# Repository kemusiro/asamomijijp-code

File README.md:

# asamomijijp-code

[asamomiji.jp](https://asamomiji.jp/)の記事に付随する公開用ソースコードを管理するリポジトリです。記事中の短いコード例ではなく、複数ファイルからなる完全版、検証用コード、過去にGitで管理されていなかった自作プログラムを主な対象とします。

コードは記事単位で`projects/<article-slug>/`へ配置します。歴史的コードについては、原作成時期、収録時の変換、検証環境、既知の制約を各プロジェクトのREADMEに記録します。

詳細は[リポジトリ運用方針](docs/repository-policy.md)を参照してください。

## 収録プロジェクト

- [YM2203サウンドモジュール](projects/ym2203-sound-module/README.md) — 採用Rev C/P2基板設計、C SDK・I2C HOSTプレーヤー、USB-MIDIと独立した再現・検証手順
- [超エレキ万博2026 展示版](projects/cho-eleki-expo-2026-clusters/README.md) — Pi 4車体進化、Pico 16台の車体・球体巡回描画、Pi 5の2画面、導入・監視・停止復旧コードとテスト
- [Terraformで構築するALBとprivate subnetのEC2](projects/terraform-aws-iac-basics/README.md) — VPC、public/private subnet、NAT Gateway、ALB、EC2を含むAWS学習用構成
- [AQM1602XA Arduino／MicroPythonクラス](projects/aqm1602-arduino-notes/README.md) — 文字表示・外字・スクロール・電源回路設定、Pico 2 W・UNO R4 WiFi／Minimaでの実機確認と自動テスト
- [UiFlow2生成Python→編集可能Block変換](projects/uiflow2-python-to-blocks/README.md) — Core2／UiFlow2 V2.5.3固定プロファイルの厳密変換、最善努力変換、`.m5f2`構造調査、Web IDE・実機検証記録
- [Raspberry Pi Pico 2 Wクラスタ実験](projects/raspberry-pi-pico-cluster/README.md) — Raspberry Pi 5と複数Pico 2 WによるMandelbrot／レイトレーシング並列計算、実測結果、進捗動画
- [Raspberry Pi Pico 2 WのMicroPython DMA実験](projects/raspberry-pi-pico-2-w-micropython-dma/README.md) — メモリー間DMA、PIO TX連携、PIO＋DMA簡易ロジックアナライザーのコードと実測ログ
- [MicroPythonコードエミッタの実機ベンチマーク](projects/micropython-performance-techniques/README.md) — Pico 2 W上でbytecode、native、Viper、Thumbインラインアセンブラを比較した検証コードと測定記録
- [MMLプレイヤー](projects/mml-player/README.md) — 2002年に作成したJava製MMLプレイヤーの歴史的ソースコード
- [micro:bit 5-queen](projects/microbit-five-queens/README.md) — 2018年にPythonとC++で5-queen問題を解いた実験コード

## ライセンス

所有者が作成して本リポジトリで公開するコードは、個別の明示がない限り[BSD 2-Clause License](LICENSE)に従います。第三者コードや別ライセンスの対象は、各プロジェクトで個別に明示します。

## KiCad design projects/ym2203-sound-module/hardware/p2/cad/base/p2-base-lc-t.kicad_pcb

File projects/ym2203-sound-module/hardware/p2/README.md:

# P2 採用設計 — base T / YM2203 module T / editor N、FAB U

編集可能なCADは`cad/`、発注に使ったCAMは`artifacts/*/gerbers/`。
ベース100×100mm・4層、音源100×80mm・2層、編集100×76mm・2層。基板各5枚、実装1セットを想定。
KiCad10.0.5。**発注済み・P2 HAL未移植・実機未受入**。Rev CのUF2をP2へ書かない。

[組立](ASSEMBLY.md)／[音声・機構](ASSEMBLY-AUDIO.md)／[互換性要件](COMPATIBILITY.md)／[発注条件](ORDER.md)／[一般BOM](procurement/README.md)。
[実装BOM](assembly/design-bom-1set.csv)は302参照、[G40](assembly/g40-pinout.csv)、[追加配線](assembly/module-wire-map.csv)、[GPIO](interfaces/gpio-map.csv)を併用する。

採用CAD/CAM、配線済み形状、原本の受入記録は変更していない。
`requirements/approved-topology.json`は採用した現在の全端子・値・フットプリントを固定する。旧レビューや購入カートを読む検査は不要。
`provenance/`は元の製造記録であり、移設後の検査入力ではない。元レポートの日時・ハッシュを更新して合格を装わない。

[ベース1枚図](readable/base/schematic.svg)／[音源1枚図](readable/module/schematic.svg)／[編集1枚図](readable/panel/schematic.svg)。

## 再現・検証

Python3とGerbonara1.6.3を使う。`<pcb-python>`は`pcbnew`をimportできるKiCad付属Python。
`<cam-python>`はGerbonaraを入れたPython。どちらも作業ディレクトリは本書の場所。

```sh
python3 tools/contract.py
python3 tools/test_contract.py
<pcb-python> tools/check_native.py
<cam-python> tools/verify_cam.py . --no-previews
<cam-python> tools/test_cam.py .
python3 tools/package.py
```

ZIPは`local-output/gerbers/`に再生成する。3件とも発注時ZIPとSHA-256が一致することを`expected-archives.json`で検査する。
新しいKiCad出力の検査は`tools/regenerate.py`を使う。正本を直接変更せず別の作業コピーへ再出力し、ERC/DRC・回路図整合、全銅形状・穴・層構成を検査する。
Gerber再出力では作成時刻コメントだけ変わり得るため、発注ZIPの完全一致とCAD再出力の一致を区別する。

```sh
python3 tools/regenerate.py --work /tmp/p2-native-check --pcb-python <pcb-python> --cam-python <cam-python>
python3 readable/tools/generate.py base module panel
python3 readable/tools/check.py --boards base module panel
```

読図用の再生成コマンドは別の作業コピーで実行する。生成後のレポートは日時等が変わるため、配布時のソースハッシュ検査とは区別する。
旧配線試行や旧購入資料を用意する必要はない。読図用回路図は基板ごと1枚に再生成し、実際のネイティブ接続と照合する。
静的検査とモデル試験は電源・USB・音声・機構の実機試験を代替しない。

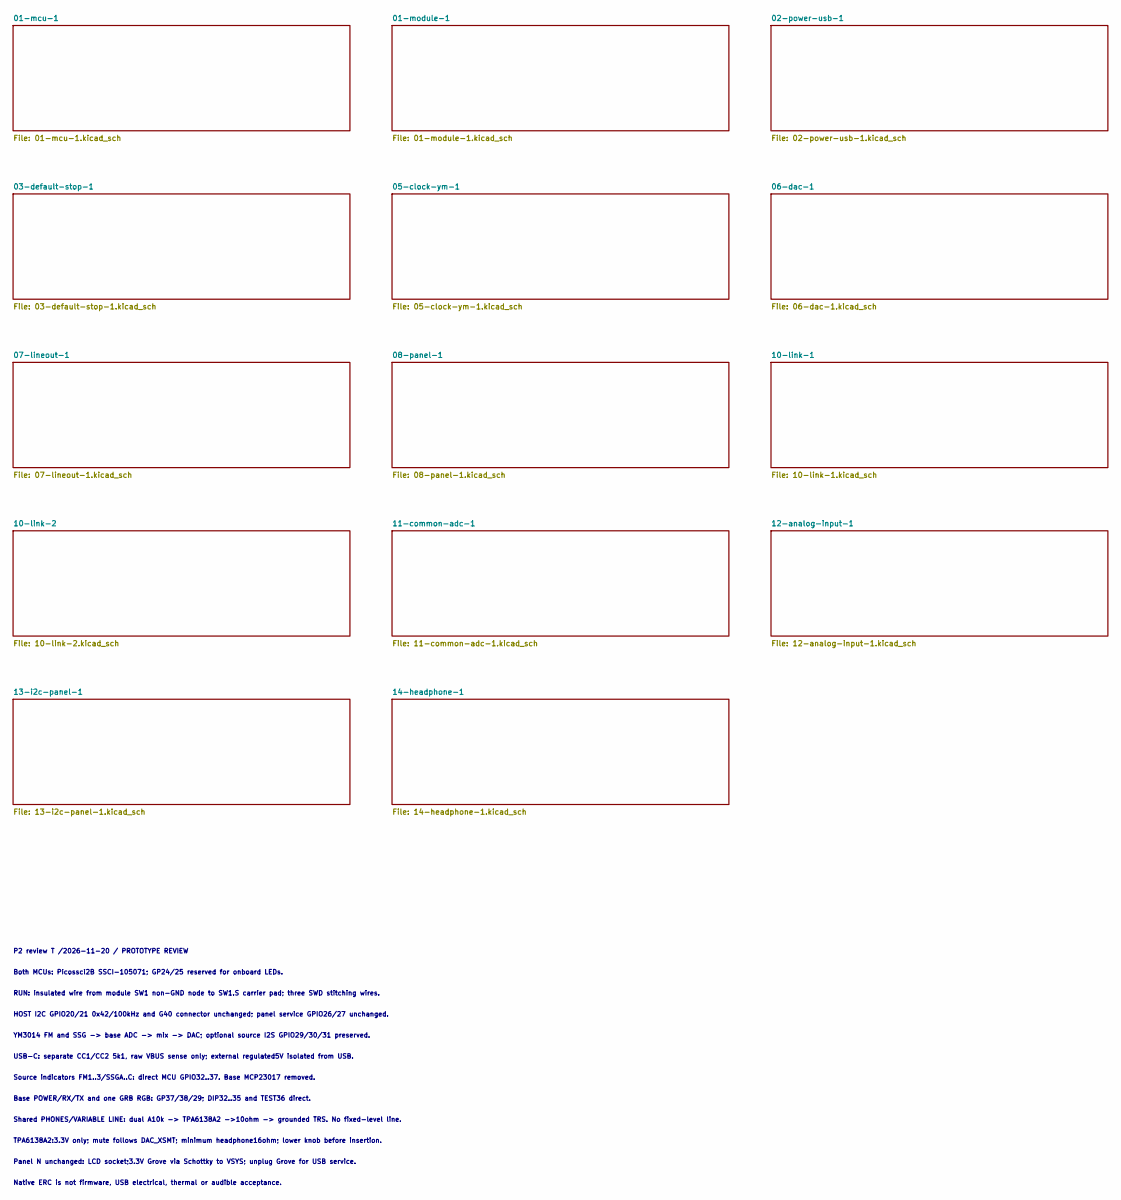
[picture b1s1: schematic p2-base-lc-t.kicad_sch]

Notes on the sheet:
P2 review T /2026-11-20 / PROTOTYPE REVIEW
Both MCUs: Picossci2B SSCI-105071; GP24/25 reserved for onboard LEDs.
RUN: insulated wire from module SW1 non-GND node to SW1.S carrier pad; three SWD stitching wires.
HOST I2C GPIO20/21 0x42/100kHz and G40 connector unchanged; panel service GPIO26/27 unchanged.
YM3014 FM and SSG -> base ADC -> mix -> DAC; optional source I2S GPIO29/30/31 preserved.
USB-C: separate CC1/CC2 5k1, raw VBUS sense only; external regulated5V isolated from USB.
Source indicators FM1..3/SSGA..C: direct MCU GPIO32..37. Base MCP23017 removed.
Base POWER/RX/TX and one GRB RGB: GP37/38/29; DIP32..35 and TEST36 direct.
Shared PHONES/VARIABLE LINE: dual A10k -> TPA6138A2 ->10ohm -> grounded TRS. No fixed-level line.
TPA6138A2:3.3V only; mute follows DAC_XSMT; minimum headphone16ohm; lower knob before insertion.
Panel N unchanged: LCD socket;3.3V Grove via Schottky to VSYS; unplug Grove for USB service.
Native ERC is not firmware, USB electrical, thermal or audible acceptance.

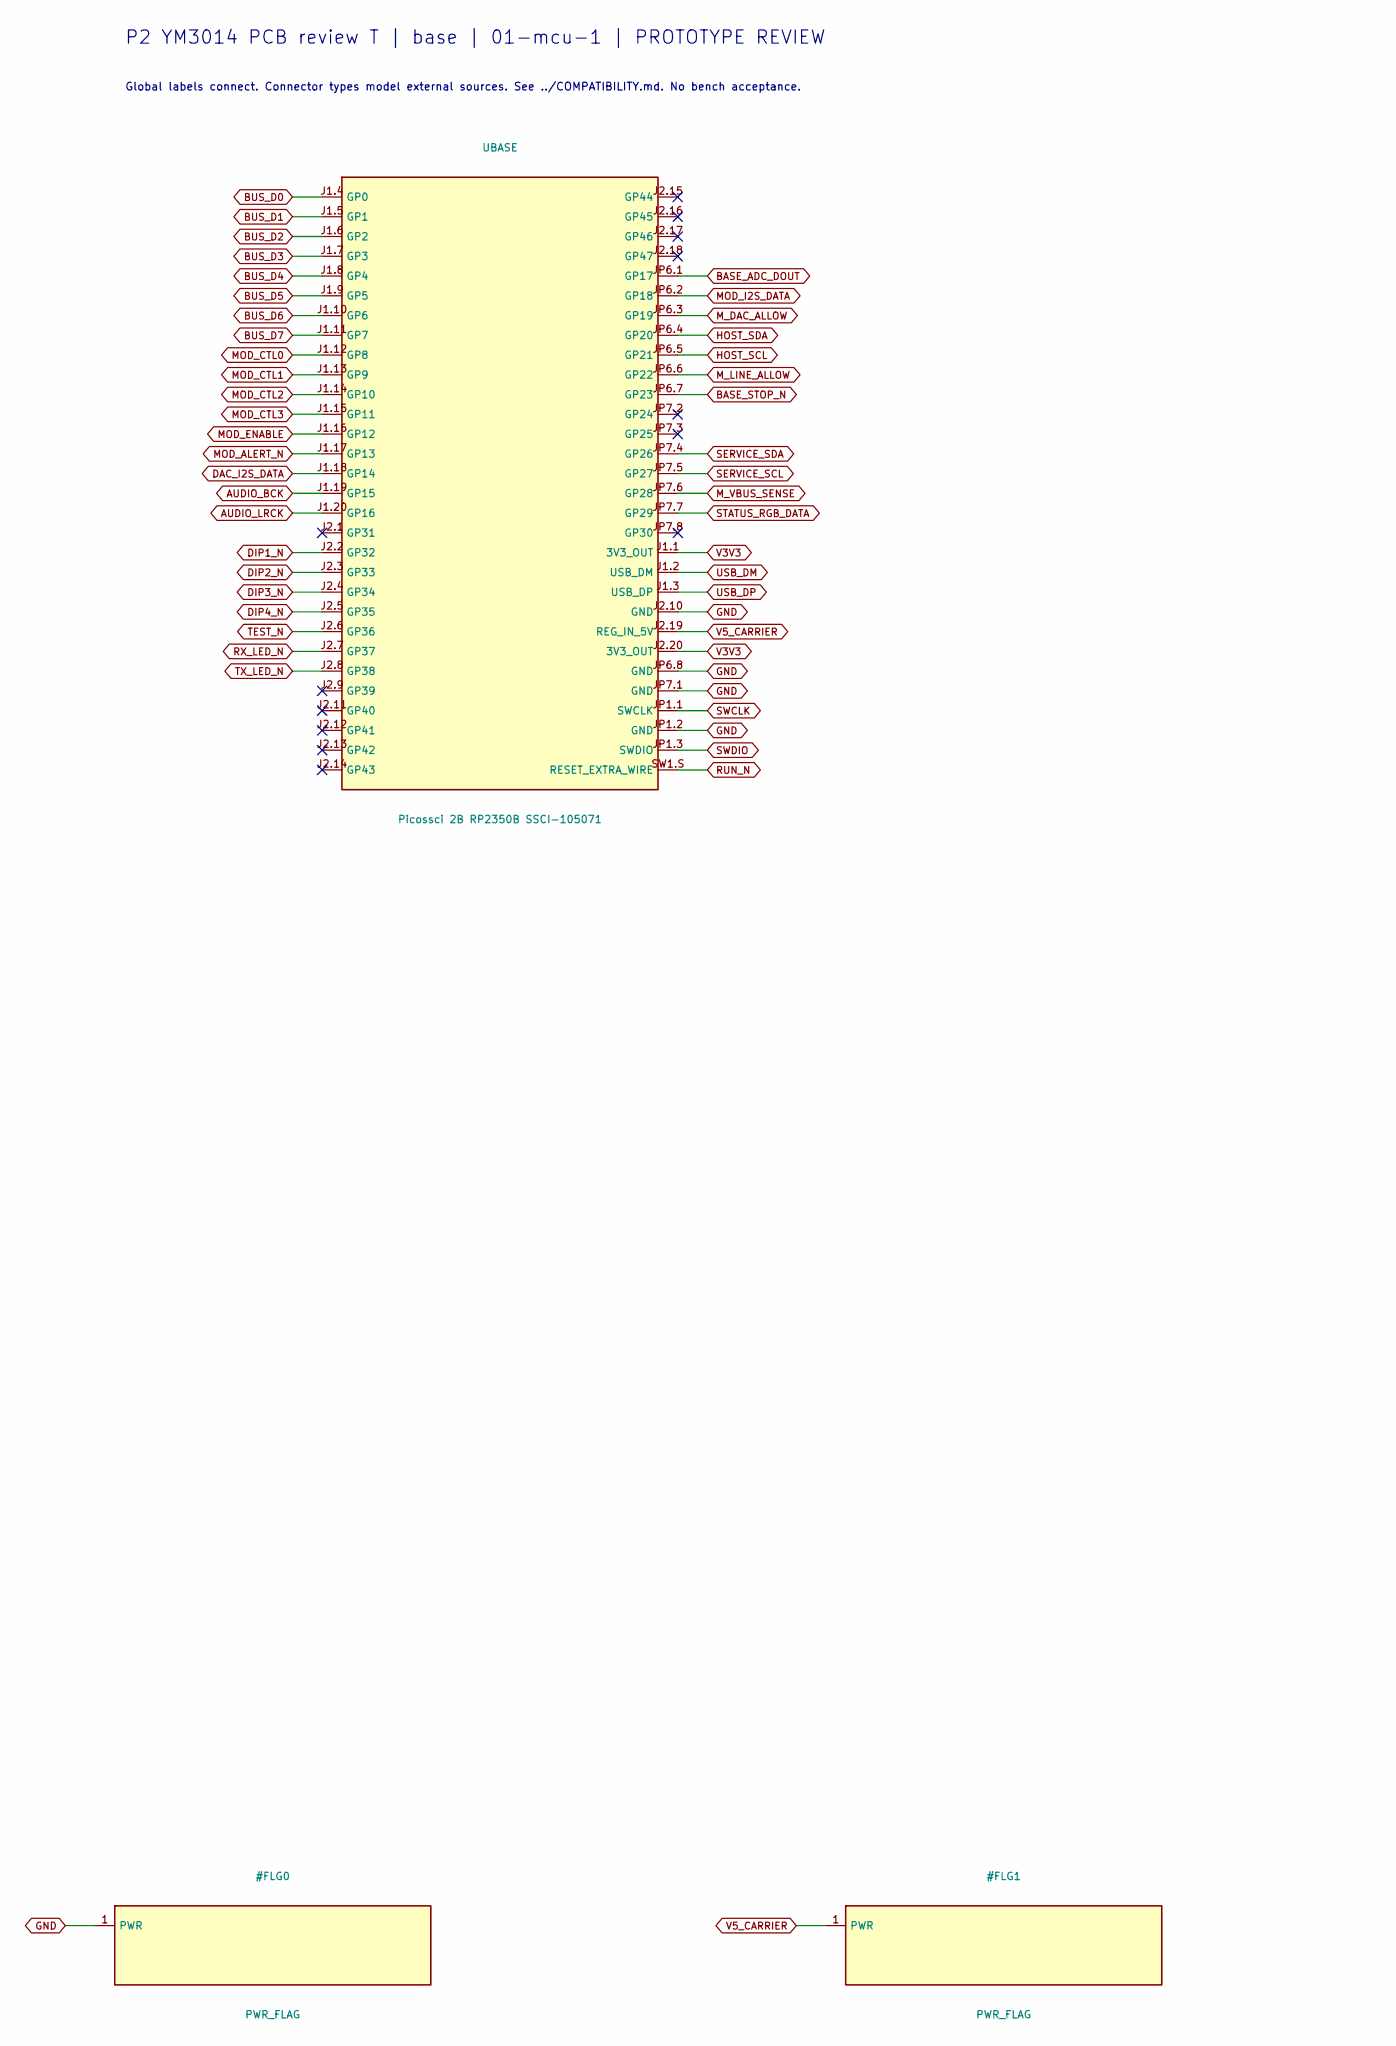
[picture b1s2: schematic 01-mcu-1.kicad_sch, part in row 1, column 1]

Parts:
UBASE: Picossci 2B RP2350B SSCI-105071; Picossci2B_DirectSolder_DebugWire

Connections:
AUDIO_BCK: UBASE.J1.19 (GP15); also elsewhere on the board
AUDIO_LRCK: UBASE.J1.20 (GP16); also elsewhere on the board
BASE_ADC_DOUT: UBASE.JP6.1 (GP17); also elsewhere on the board
BASE_STOP_N: UBASE.JP6.7 (GP23); also elsewhere on the board
BUS_D0: UBASE.J1.4 (GP0); also elsewhere on the board
BUS_D1: UBASE.J1.5 (GP1); also elsewhere on the board
BUS_D2: UBASE.J1.6 (GP2); also elsewhere on the board
BUS_D3: UBASE.J1.7 (GP3); also elsewhere on the board
BUS_D4: UBASE.J1.8 (GP4); also elsewhere on the board
BUS_D5: UBASE.J1.9 (GP5); also elsewhere on the board
BUS_D6: UBASE.J1.10 (GP6); also elsewhere on the board
BUS_D7: UBASE.J1.11 (GP7); also elsewhere on the board
DAC_I2S_DATA: UBASE.J1.18 (GP14); also elsewhere on the board
DIP1_N: UBASE.J2.2 (GP32); also elsewhere on the board
DIP2_N: UBASE.J2.3 (GP33); also elsewhere on the board
DIP3_N: UBASE.J2.4 (GP34); also elsewhere on the board
DIP4_N: UBASE.J2.5 (GP35); also elsewhere on the board
GND: UBASE.J2.10 (GND), UBASE.JP1.2 (GND), UBASE.JP6.8 (GND), UBASE.JP7.1 (GND); also elsewhere on the board
HOST_SCL: UBASE.JP6.5 (GP21); also elsewhere on the board
HOST_SDA: UBASE.JP6.4 (GP20); also elsewhere on the board
MOD_ALERT_N: UBASE.J1.17 (GP13); also elsewhere on the board
MOD_CTL0: UBASE.J1.12 (GP8); also elsewhere on the board
MOD_CTL1: UBASE.J1.13 (GP9); also elsewhere on the board
MOD_CTL2: UBASE.J1.14 (GP10); also elsewhere on the board
MOD_CTL3: UBASE.J1.15 (GP11); also elsewhere on the board
MOD_ENABLE: UBASE.J1.16 (GP12); also elsewhere on the board
MOD_I2S_DATA: UBASE.JP6.2 (GP18); also elsewhere on the board
M_DAC_ALLOW: UBASE.JP6.3 (GP19); also elsewhere on the board
M_LINE_ALLOW: UBASE.JP6.6 (GP22); also elsewhere on the board
M_VBUS_SENSE: UBASE.JP7.6 (GP28); also elsewhere on the board
RUN_N: UBASE.SW1.S (RESET_EXTRA_WIRE); also elsewhere on the board
RX_LED_N: UBASE.J2.7 (GP37); also elsewhere on the board
SERVICE_SCL: UBASE.JP7.5 (GP27); also elsewhere on the board
SERVICE_SDA: UBASE.JP7.4 (GP26); also elsewhere on the board
STATUS_RGB_DATA: UBASE.JP7.7 (GP29); also elsewhere on the board
SWCLK: UBASE.JP1.1 (SWCLK); also elsewhere on the board
SWDIO: UBASE.JP1.3 (SWDIO); also elsewhere on the board
TEST_N: UBASE.J2.6 (GP36); also elsewhere on the board
TX_LED_N: UBASE.J2.8 (GP38); also elsewhere on the board
USB_DM: UBASE.J1.2 (USB_DM); also elsewhere on the board
USB_DP: UBASE.J1.3 (USB_DP); also elsewhere on the board
V3V3: UBASE.J1.1 (3V3_OUT), UBASE.J2.20 (3V3_OUT); also elsewhere on the board
V5_CARRIER: UBASE.J2.19 (REG_IN_5V); also elsewhere on the board

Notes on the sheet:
P2 YM3014 PCB review T | base | 01-mcu-1 | PROTOTYPE REVIEW
Global labels connect. Connector types model external sources. See ../COMPATIBILITY.md. No bench acceptance.

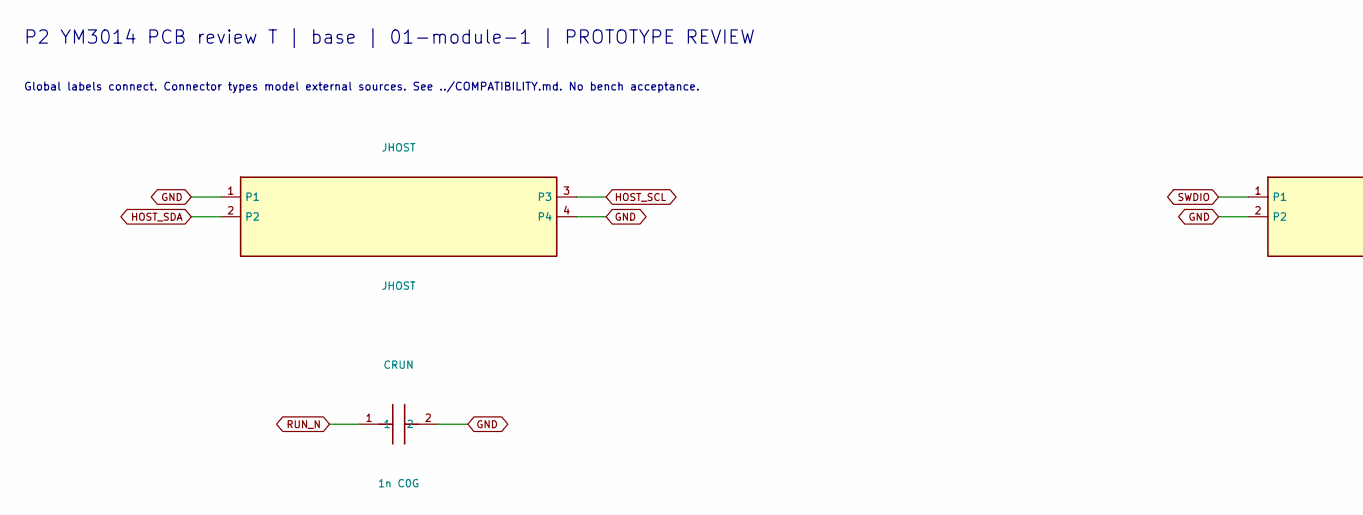
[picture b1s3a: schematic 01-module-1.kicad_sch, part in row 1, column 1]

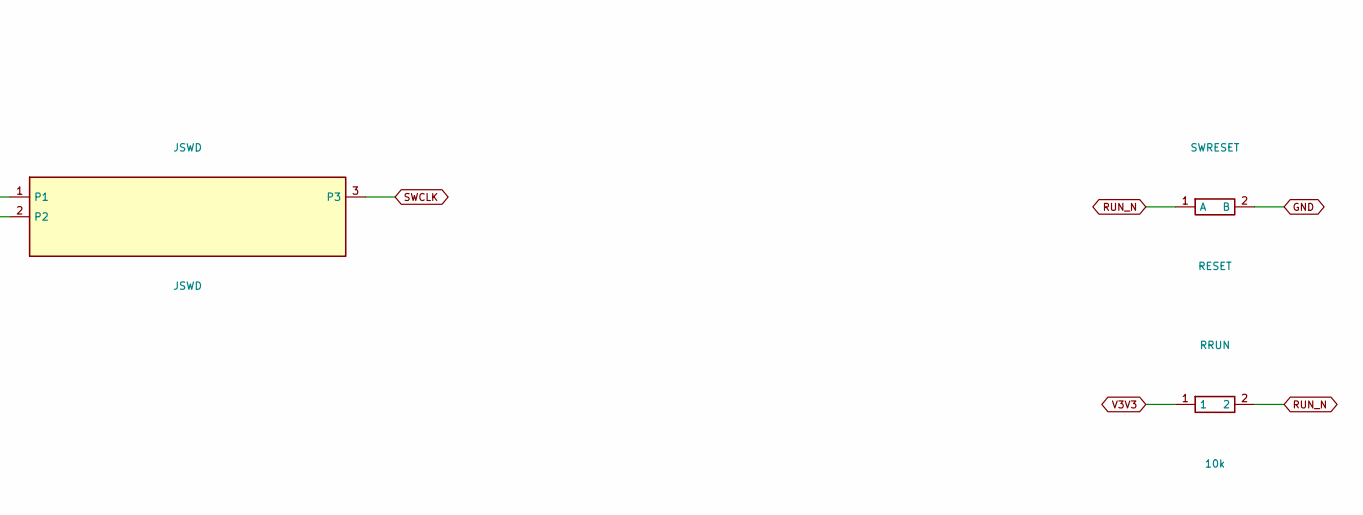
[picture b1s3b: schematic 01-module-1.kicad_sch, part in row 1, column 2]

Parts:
CRUN: 1n C0G; C_0805_2012Metric
JHOST: JHOST; PinHeader_1x04_P2.54mm_Vertical
JSWD: JSWD; PinHeader_1x03_P2.54mm_Vertical
RRUN: 10k; R_0805_2012Metric
SWRESET: RESET; SW_PUSH_6mm_H4.3mm

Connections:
GND: CRUN.2, JHOST.1, JHOST.4, JSWD.2, SWRESET.2 (B); also elsewhere on the board
HOST_SCL: JHOST.3; also elsewhere on the board
HOST_SDA: JHOST.2; also elsewhere on the board
RUN_N: CRUN.1, RRUN.2, SWRESET.1 (A); also elsewhere on the board
SWCLK: JSWD.3; also elsewhere on the board
SWDIO: JSWD.1; also elsewhere on the board
V3V3: RRUN.1; also elsewhere on the board

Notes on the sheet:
P2 YM3014 PCB review T | base | 01-module-1 | PROTOTYPE REVIEW
Global labels connect. Connector types model external sources. See ../COMPATIBILITY.md. No bench acceptance.

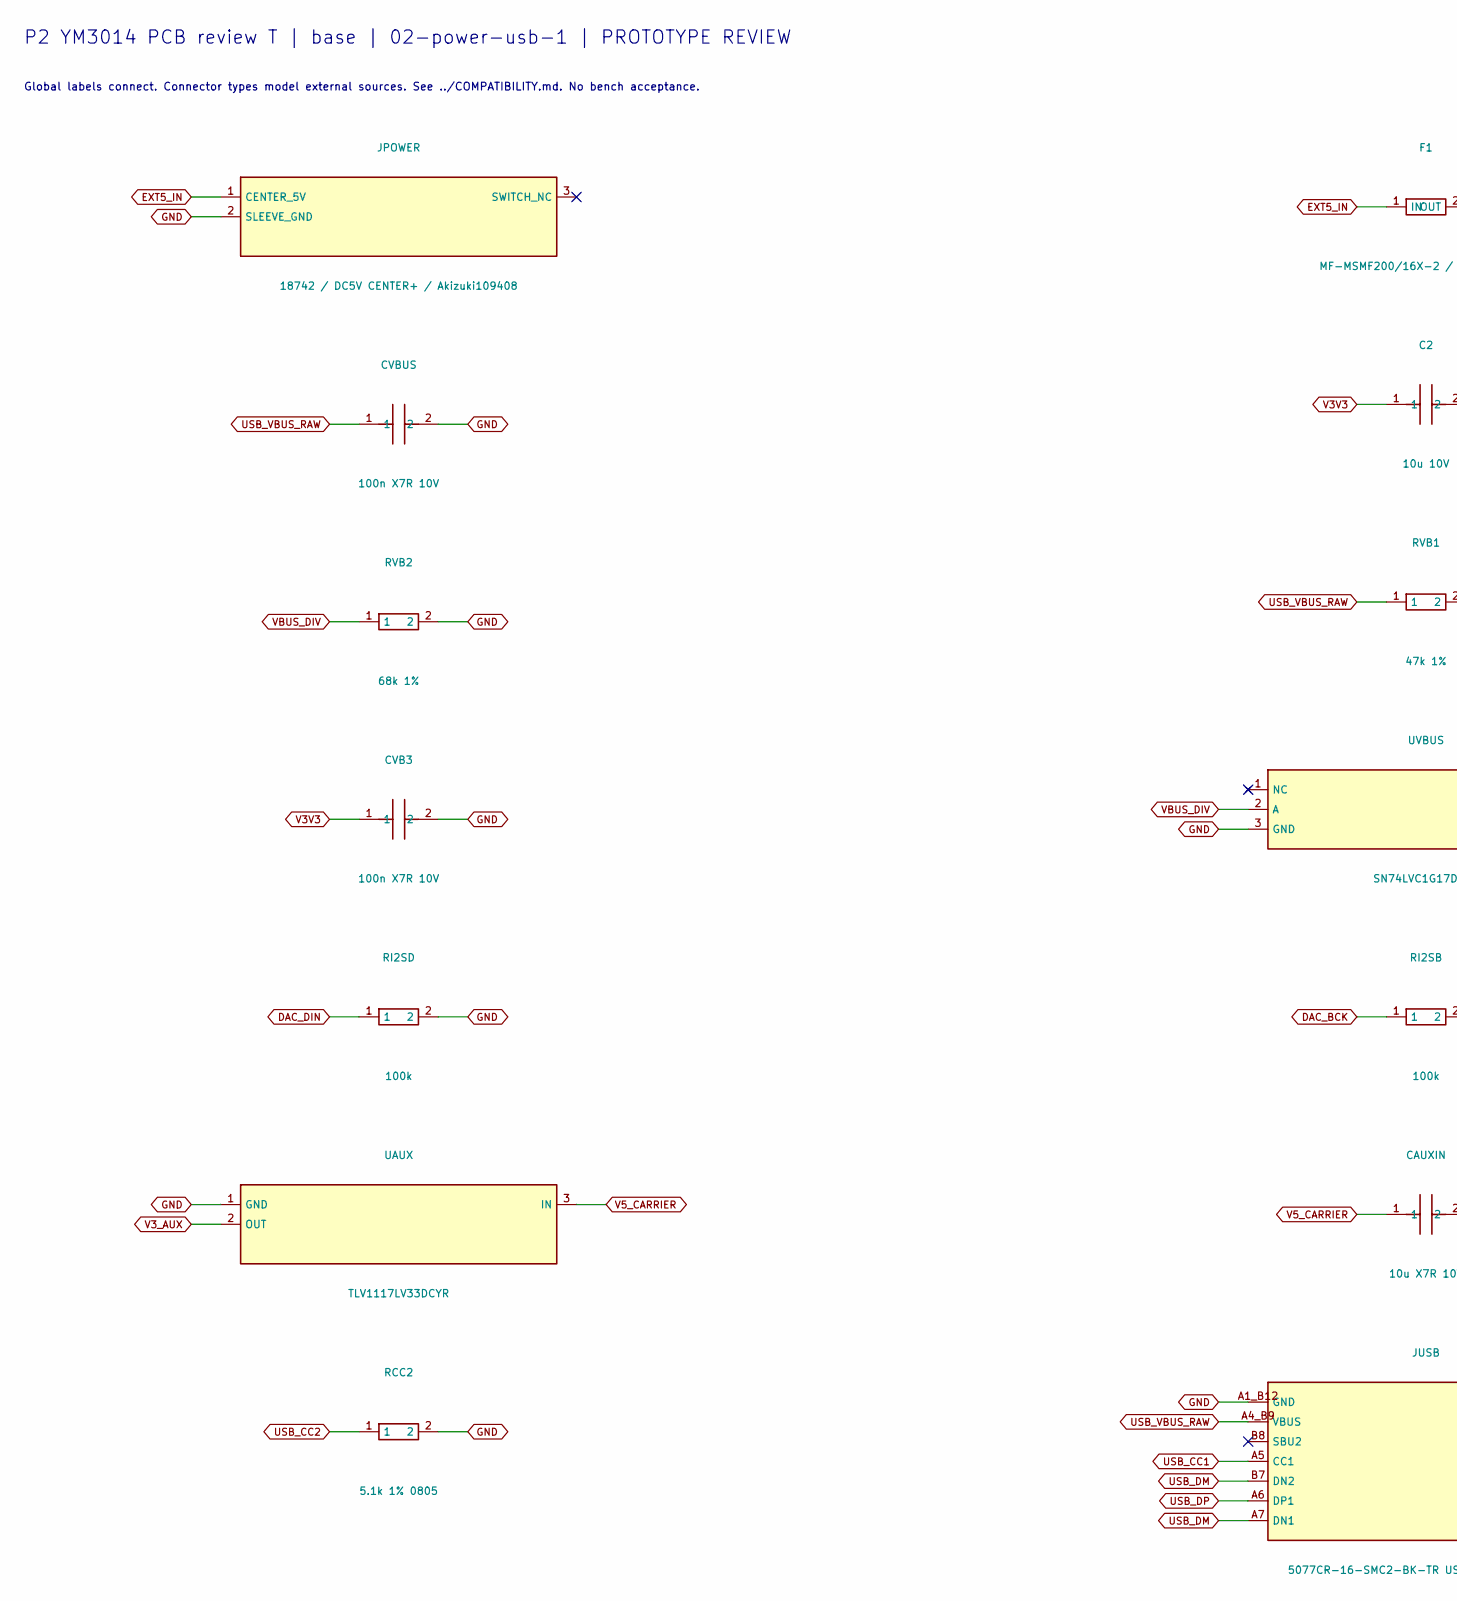
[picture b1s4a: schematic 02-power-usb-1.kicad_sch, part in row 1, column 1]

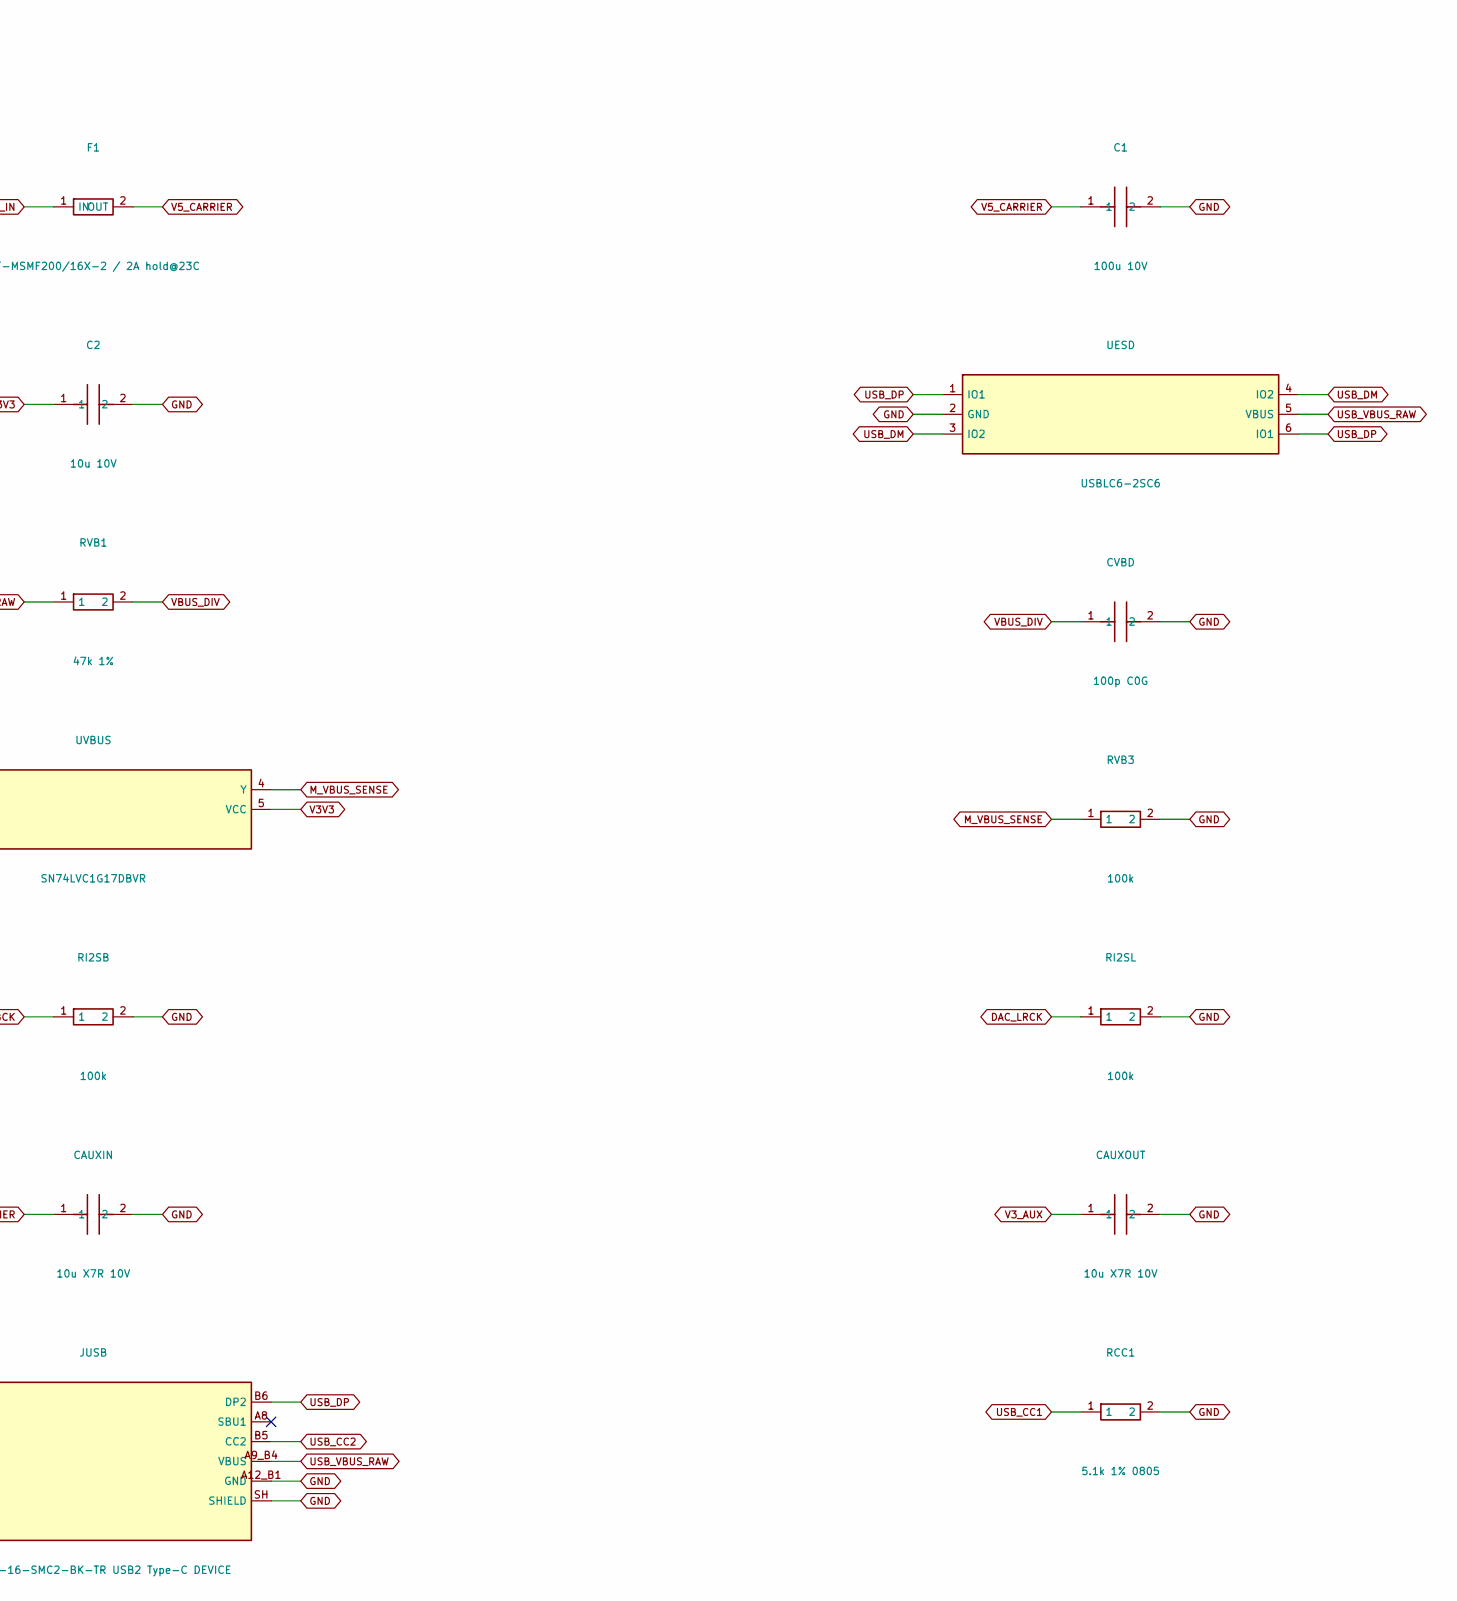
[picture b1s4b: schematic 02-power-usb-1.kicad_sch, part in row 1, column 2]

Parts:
C1: 100u 10V; CP_Radial_D6.3mm_P2.50mm
C2: 10u 10V; C_0805_2012Metric
CAUXIN: 10u X7R 10V; C_0805_2012Metric
CAUXOUT: 10u X7R 10V; C_0805_2012Metric
CVB3: 100n X7R 10V; C_0805_2012Metric
CVBD: 100p C0G; C_0805_2012Metric
CVBUS: 100n X7R 10V; C_0805_2012Metric
F1: MF-MSMF200/16X-2 / 2A hold@23C; Fuse_1812_4532Metric
JPOWER: 18742 / DC5V CENTER+ / Akizuki109408; DCJack_4UCON_18742
JUSB: 5077CR-16-SMC2-BK-TR USB2 Type-C DEVICE; USB_C_Neltron_5077CR_16_SMC2
RCC1, RCC2: 5.1k 1% 0805; R_0805_2012Metric
RI2SB, RI2SD, RI2SL: 100k; R_0805_2012Metric
RVB1: 47k 1%; R_0805_2012Metric
RVB2: 68k 1%; R_0805_2012Metric
RVB3: 100k; R_0805_2012Metric
UAUX: TLV1117LV33DCYR; SOT-223-3_TabPin2
UESD: USBLC6-2SC6; SOT-23-6
UVBUS: SN74LVC1G17DBVR; SOT-23-5

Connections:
DAC_BCK: RI2SB.1; also elsewhere on the board
DAC_DIN: RI2SD.1; also elsewhere on the board
DAC_LRCK: RI2SL.1; also elsewhere on the board
EXT5_IN: F1.1 (IN), JPOWER.1 (CENTER_5V)
GND: C1.2, C2.2, CAUXIN.2, CAUXOUT.2, CVB3.2, CVBD.2, CVBUS.2, JPOWER.2 (SLEEVE_GND), JUSB.A1_B12 (GND), JUSB.A12_B1 (GND), JUSB.SH (SHIELD), RCC1.2, RCC2.2, RI2SB.2, RI2SD.2, RI2SL.2, RVB2.2, RVB3.2, UAUX.1 (GND), UESD.2 (GND), UVBUS.3 (GND); also elsewhere on the board
M_VBUS_SENSE: RVB3.1, UVBUS.4 (Y); also elsewhere on the board
USB_CC1: JUSB.A5 (CC1), RCC1.1
USB_CC2: JUSB.B5 (CC2), RCC2.1
USB_DM: JUSB.A7 (DN1), JUSB.B7 (DN2), UESD.3 (IO2), UESD.4 (IO2); also elsewhere on the board
USB_DP: JUSB.A6 (DP1), JUSB.B6 (DP2), UESD.1 (IO1), UESD.6 (IO1); also elsewhere on the board
USB_VBUS_RAW: CVBUS.1, JUSB.A4_B9 (VBUS), JUSB.A9_B4 (VBUS), RVB1.1, UESD.5 (VBUS)
V3V3: C2.1, CVB3.1, UVBUS.5 (VCC); also elsewhere on the board
V3_AUX: CAUXOUT.1, UAUX.2 (OUT); also elsewhere on the board
V5_CARRIER: C1.1, CAUXIN.1, F1.2 (OUT), UAUX.3 (IN); also elsewhere on the board
VBUS_DIV: CVBD.1, RVB1.2, RVB2.1, UVBUS.2 (A)

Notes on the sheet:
P2 YM3014 PCB review T | base | 02-power-usb-1 | PROTOTYPE REVIEW
Global labels connect. Connector types model external sources. See ../COMPATIBILITY.md. No bench acceptance.

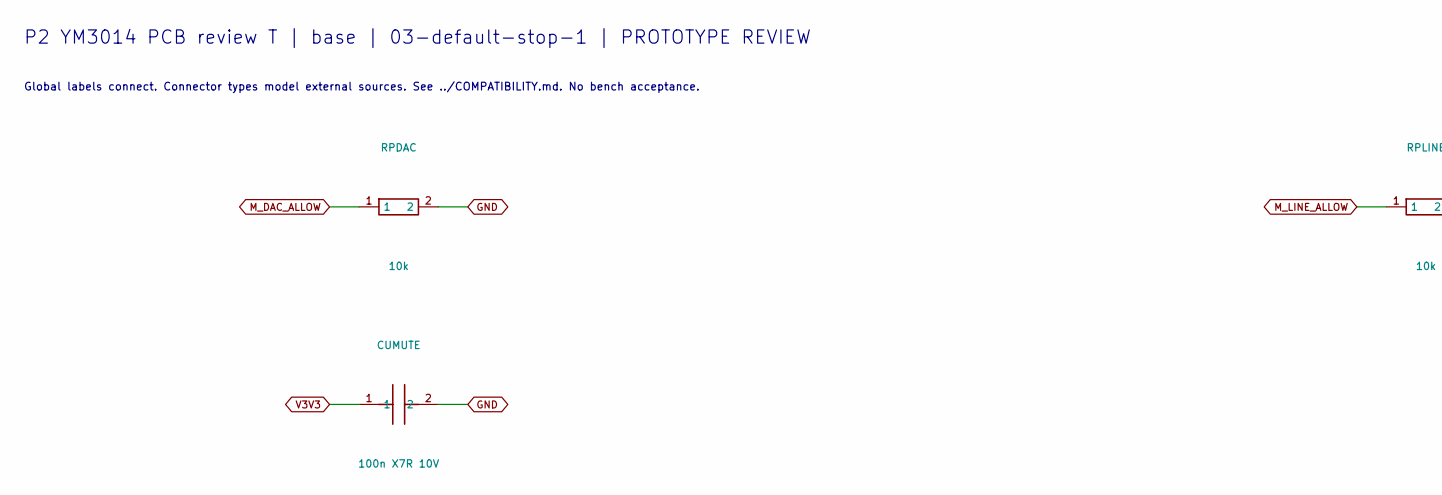
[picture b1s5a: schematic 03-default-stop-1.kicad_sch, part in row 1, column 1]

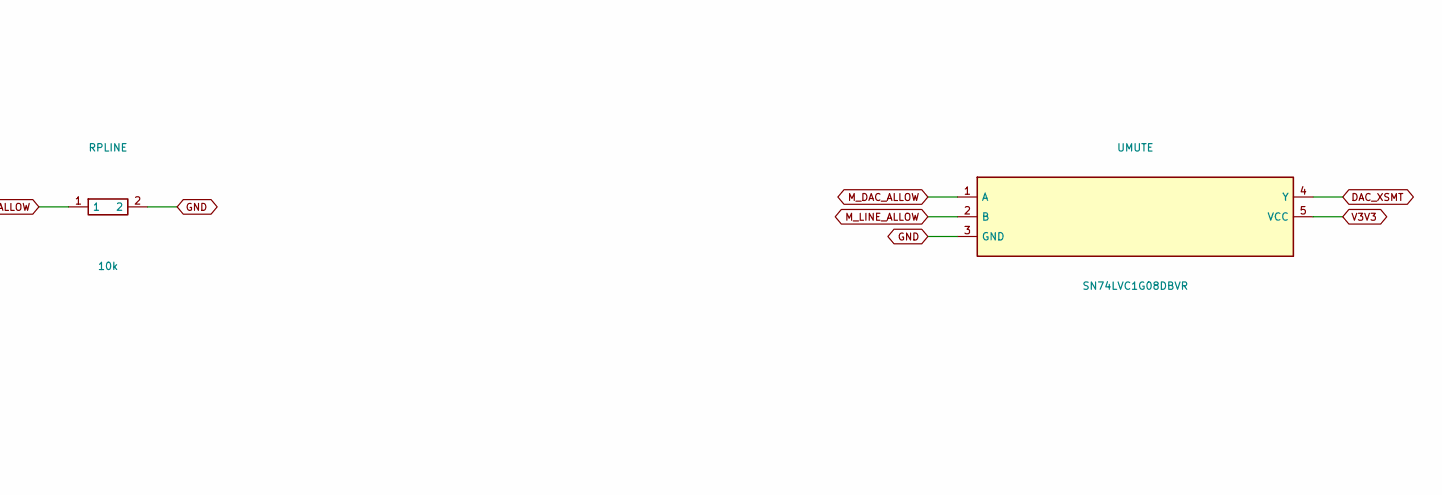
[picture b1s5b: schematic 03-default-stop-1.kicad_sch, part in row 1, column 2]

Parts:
CUMUTE: 100n X7R 10V; C_0805_2012Metric
RPDAC: 10k; R_0805_2012Metric
RPLINE: 10k; R_0805_2012Metric
UMUTE: SN74LVC1G08DBVR; SOT-23-5

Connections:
DAC_XSMT: UMUTE.4 (Y); also elsewhere on the board
GND: CUMUTE.2, RPDAC.2, RPLINE.2, UMUTE.3 (GND); also elsewhere on the board
M_DAC_ALLOW: RPDAC.1, UMUTE.1 (A); also elsewhere on the board
M_LINE_ALLOW: RPLINE.1, UMUTE.2 (B); also elsewhere on the board
V3V3: CUMUTE.1, UMUTE.5 (VCC); also elsewhere on the board

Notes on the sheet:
P2 YM3014 PCB review T | base | 03-default-stop-1 | PROTOTYPE REVIEW
Global labels connect. Connector types model external sources. See ../COMPATIBILITY.md. No bench acceptance.

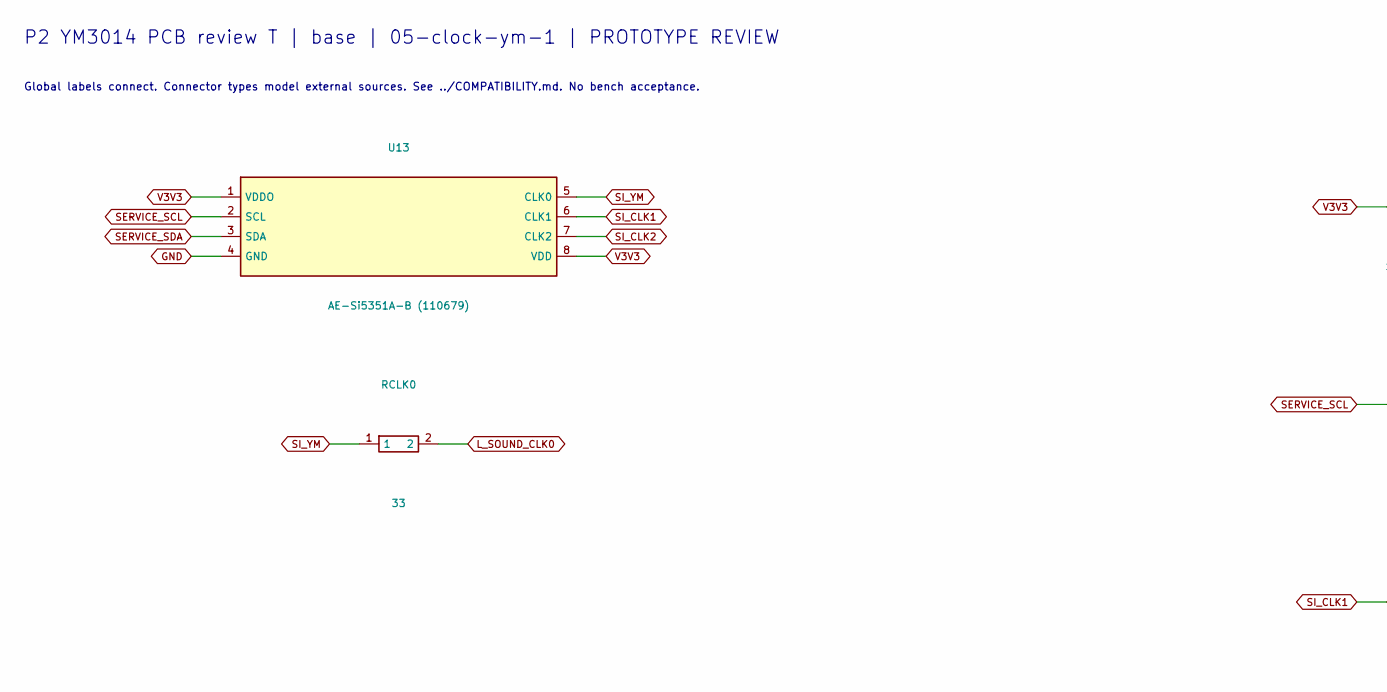
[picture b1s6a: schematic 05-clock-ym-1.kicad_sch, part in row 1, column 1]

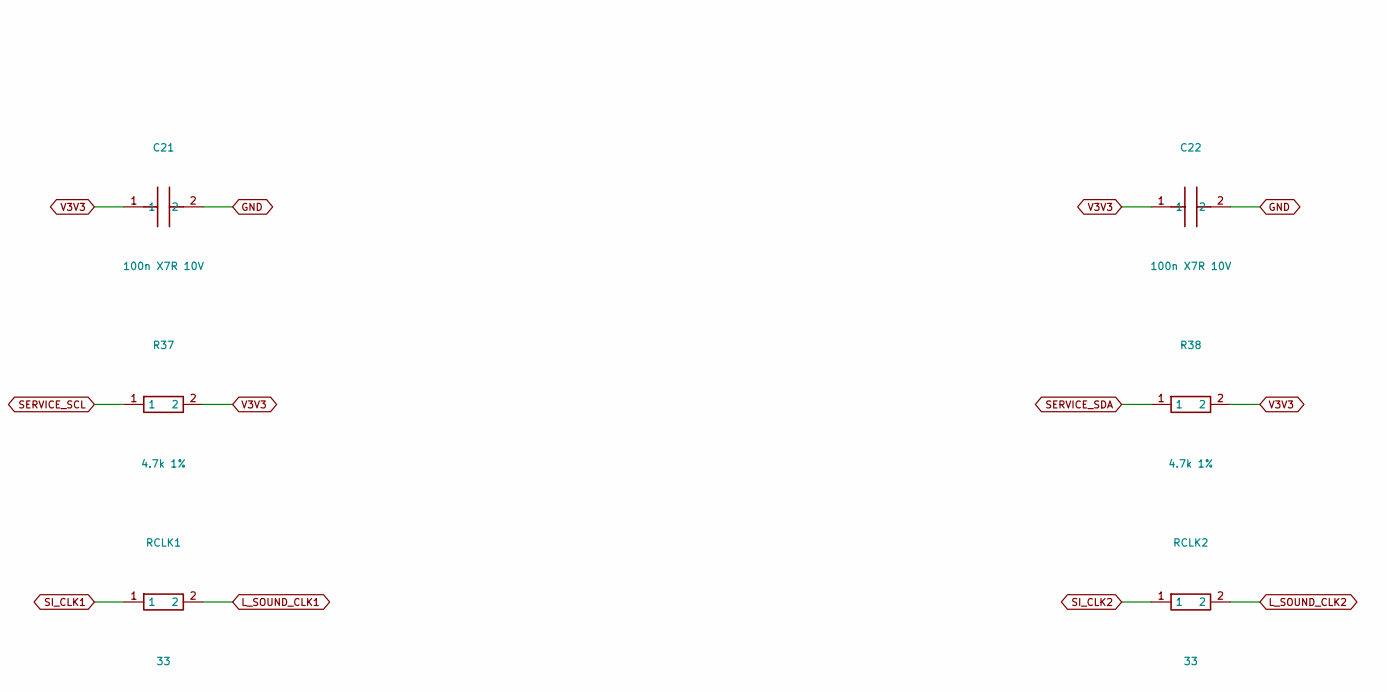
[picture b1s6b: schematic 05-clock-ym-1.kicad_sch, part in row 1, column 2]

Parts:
C21, C22: 100n X7R 10V; C_0805_2012Metric
R37, R38: 4.7k 1%; R_0805_2012Metric
RCLK0, RCLK1, RCLK2: 33; R_0805_2012Metric
U13: AE-Si5351A-B (110679); AE_Si5351A_B_10x10mm

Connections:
GND: C21.2, C22.2, U13.4 (GND); also elsewhere on the board
L_SOUND_CLK0: RCLK0.2; also elsewhere on the board
L_SOUND_CLK1: RCLK1.2; also elsewhere on the board
L_SOUND_CLK2: RCLK2.2; also elsewhere on the board
SERVICE_SCL: R37.1, U13.2 (SCL); also elsewhere on the board
SERVICE_SDA: R38.1, U13.3 (SDA); also elsewhere on the board
SI_CLK1: RCLK1.1, U13.6 (CLK1)
SI_CLK2: RCLK2.1, U13.7 (CLK2)
SI_YM: RCLK0.1, U13.5 (CLK0)
V3V3: C21.1, C22.1, R37.2, R38.2, U13.1 (VDDO), U13.8 (VDD); also elsewhere on the board

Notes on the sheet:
P2 YM3014 PCB review T | base | 05-clock-ym-1 | PROTOTYPE REVIEW
Global labels connect. Connector types model external sources. See ../COMPATIBILITY.md. No bench acceptance.
